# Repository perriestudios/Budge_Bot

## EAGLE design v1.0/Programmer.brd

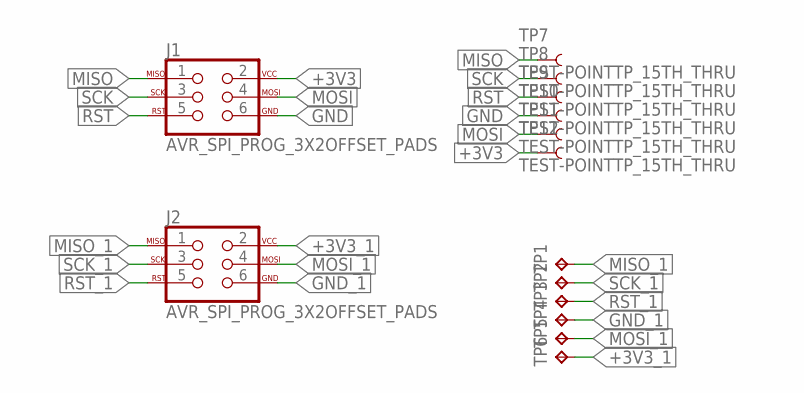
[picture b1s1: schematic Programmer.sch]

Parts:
J1, J2: AVR_SPI_PROG_3X2OFFSET_PADS; 2X3_OFFSET
TP1, TP2, TP3, TP4, TP5, TP6: TPTP12SQ; TP12SQ
TP7, TP8, TP9, TP10, TP11, TP12: TEST-POINTTP_15TH_THRU; TP_15TH

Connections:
+3V3: J1.2, TP12.P$1
+3V3_1: J2.2, TP6.TP
GND: J1.6, TP10.P$1
GND_1: J2.6, TP4.TP
MISO: J1.1, TP7.P$1
MISO_1: J2.1, TP1.TP
MOSI: J1.4, TP11.P$1
MOSI_1: J2.4, TP5.TP
RST: J1.5, TP9.P$1
RST_1: J2.5, TP3.TP
SCK: J1.3, TP8.P$1
SCK_1: J2.3, TP2.TP

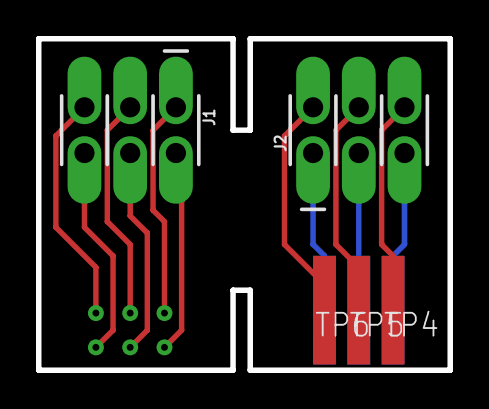
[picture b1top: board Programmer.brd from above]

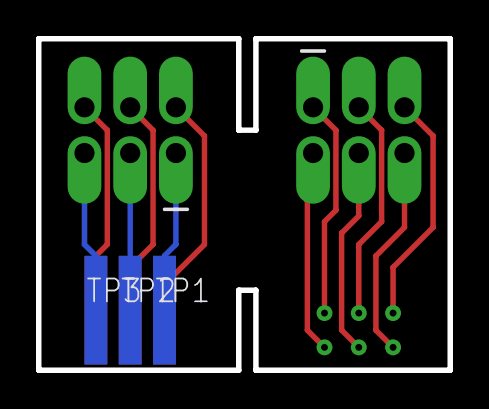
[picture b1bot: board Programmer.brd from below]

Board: 2 copper layers, 22.9 x 18.4 mm, 14 parts (3 on the bottom side), 12 nets.

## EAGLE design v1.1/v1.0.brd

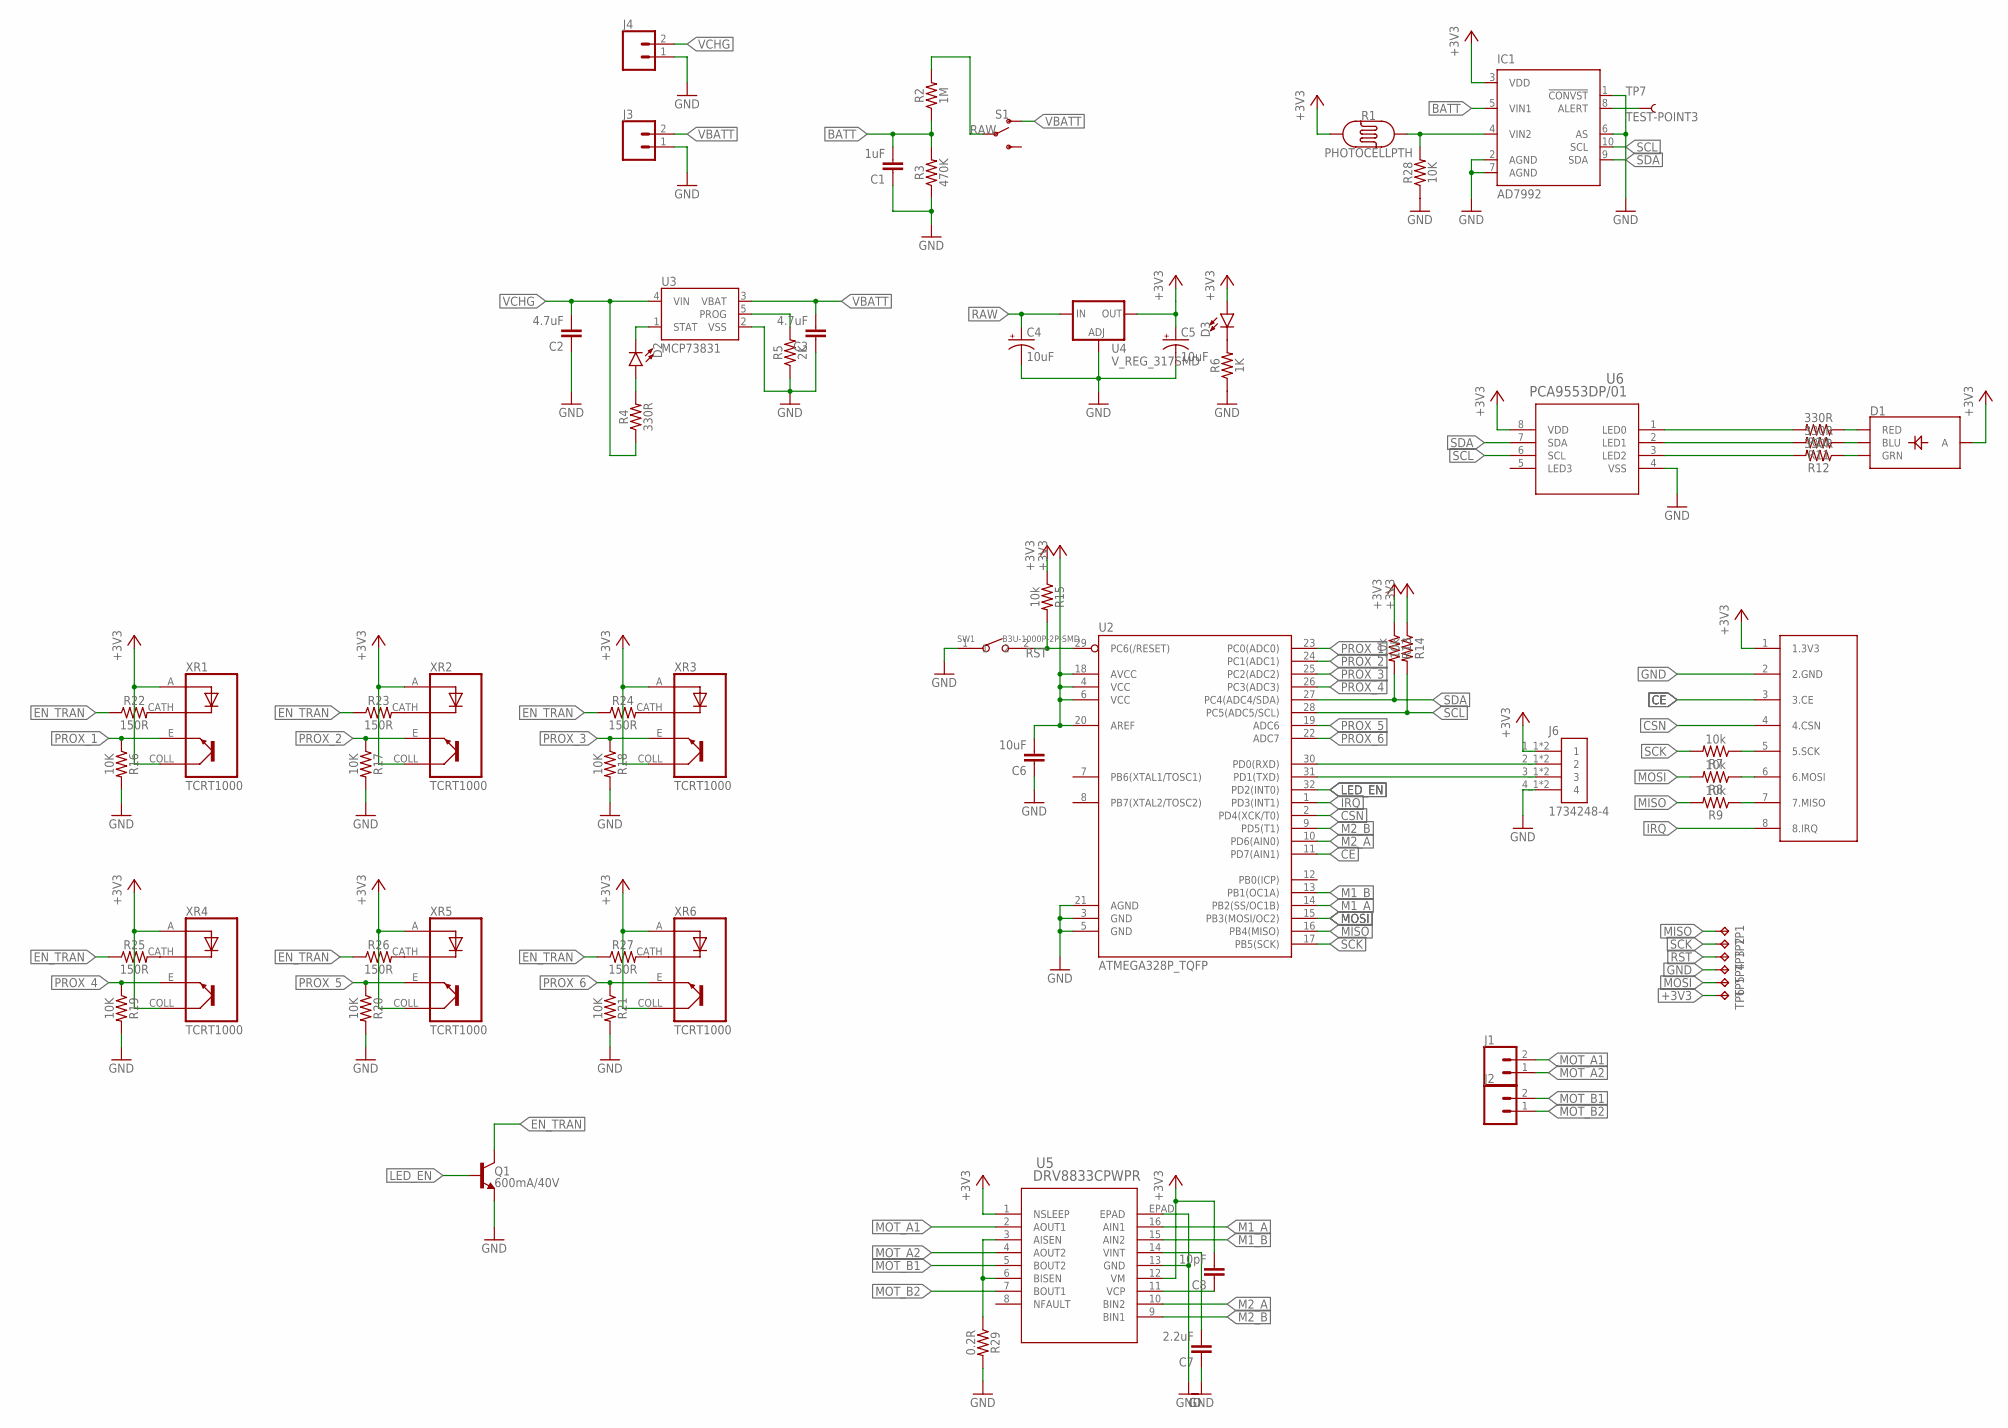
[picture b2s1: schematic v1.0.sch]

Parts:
C1: 1uF; C0603
C2, C3: 4.7uF; C0603
C4, C5: 10uF; EIA3216
C6: 10uF; C0603
C7: 2.2uF; C0603
C8: 10pF; C0603
D1: LED-RGB-CASMD; LED-TRICOLOR-SMD
D2, D3: LED0603; LED-0603
IC1: AD7992; MSOP10
J1, J2, J3, J4: CONN_02; 1X02
J6: 1734248-4; TE_1734248-4
Q1: 600mA/40V; SOT23-3
R1: PHOTOCELLPTH; PHOTOCELL
R2: 1M; 0402
R3: 470K; 0402
R4, R10, R11, R12: 330R; 0402
R5: 2K; 0402
R6: 1K; 0402
R7, R8, R9, R13, R14, R15: 10k; 0402
R16, R17, R18, R19, R20, R21, R28: 10K; 0402
R22, R23, R24, R25, R26, R27: 150R; 0402
R29: 0.2R; 0402
S1: SWITCH-SPDT-SMD-RIGHT-ANGLE; SWITCH_SPST_SMD_A
SW1: B3U-1000P-2P-SMD; SW2-2.6-3.0X2.5X1.2+0.4MM
TP1, TP2, TP3, TP4, TP5, TP6: TPB1,27; B1,27
TP7: TEST-POINT3; PAD.03X.03
U2: ATMEGA328P_TQFP; TQFP32-08
U3: MCP73831; SOT23-5
U4: V_REG_317SMD; SOT223
U5: DRV8833CPWPR; PWP16_2P31X2P46
U6: PCA9553DP/01; SOT505-1
U$1: NRF24L01+
XR1, XR2, XR3, XR4, XR5, XR6: TCRT1000; XDCR_TCRT1000

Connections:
+3V3: C5.+, C6.2, C8.2, D1.A, D3.A, IC1.3 (VDD), J6.1_1 (1), J6.1_2 (1), R1.1, R13.1, R14.1, R15.1, TP6.TP, U2.4 (VCC), U2.6 (VCC), U2.18 (AVCC), U2.20 (AREF), U4.2 (OUT), U5.1 (NSLEEP), U5.12 (VM), U6.8 (VDD), U$1.1 (1.3V3), XR1.A, XR1.COLL (CO), XR2.A, XR2.COLL (CO), XR3.A, XR3.COLL (CO), XR4.A, XR4.COLL (CO), XR5.A, XR5.COLL (CO), XR6.A, XR6.COLL (CO)
BATT: C1.2, IC1.5 (VIN1), R2.1, R3.2
CE: U2.11 (PD7(AIN1)), U$1.3 (3.CE)
CSN: U2.2 (PD4(XCK/T0)), U$1.4 (4.CSN)
EN_TRAN: Q1.3 (C), R22.1, R23.1, R24.1, R25.1, R26.1, R27.1
GND: C1.1, C2.1, C3.1, C4.-, C5.-, C6.1, C7.1, IC1.1 (!CONVST), IC1.2 (AGND), IC1.6 (AS), IC1.7 (AGND), J3.1, J4.1, J6.4_1 (4), J6.4_2 (4), Q1.2 (E), R3.1, R5.1, R6.1, R16.2, R17.2, R18.2, R19.2, R20.2, R21.2, R28.1, R29.2, SW1.1, TP4.TP, U2.3 (GND), U2.5 (GND), U2.21 (AGND), U3.2 (VSS), U4.1 (ADJ), U5.13 (GND), U5.EPAD, U6.4 (VSS), U$1.2 (2.GND)
IRQ: U2.1 (PD3(INT1)), U$1.8 (8.IRQ)
LED_EN: Q1.1 (B), U2.32 (PD2(INT0))
M1_A: U2.14 (PB2(SS/OC1B)), U5.16 (AIN1)
M1_B: U2.13 (PB1(OC1A)), U5.15 (AIN2)
M2_A: U2.10 (PD6(AIN0)), U5.10 (BIN2)
M2_B: U2.9 (PD5(T1)), U5.9 (BIN1)
MISO: R9.2, TP1.TP, U2.16 (PB4(MISO))
MOSI: R8.2, TP5.TP, U2.15 (PB3(MOSI/OC2))
MOT_A1: J1.2, U5.2 (AOUT1)
MOT_A2: J1.1, U5.4 (AOUT2)
MOT_B1: J2.2, U5.5 (BOUT2)
MOT_B2: J2.1, U5.7 (BOUT1)
unnamed: R7.1, U$1.5 (5.SCK)
unnamed: R8.1, U$1.6 (6.MOSI)
unnamed: D3.C, R6.2
unnamed: D2.C, U3.1 (STAT)
unnamed: D2.A, R4.2
unnamed: R9.1, U$1.7 (7.MISO)
unnamed: D1.R (RED), R10.1
unnamed: D1.B (BLU), R11.1
unnamed: R5.2, U3.5 (PROG)
unnamed: D1.G (GRN), R12.1
unnamed: R29.1, U5.3 (AISEN), U5.6 (BISEN)
unnamed: IC1.4 (VIN2), R1.2, R28.2
unnamed: IC1.8 (ALERT), TP7.P$1
unnamed: C7.2, U5.14 (VINT)
unnamed: C8.1, U5.11 (VCP)
unnamed: J6.3_1 (3), J6.3_2 (3), U2.31 (PD1(TXD))
unnamed: J6.2_1 (2), J6.2_2 (2), U2.30 (PD0(RXD))
unnamed: R22.2, XR1.CATH (C)
unnamed: R23.2, XR2.CATH (C)
unnamed: R24.2, XR3.CATH (C)
unnamed: R25.2, XR4.CATH (C)
unnamed: R26.2, XR5.CATH (C)
unnamed: R27.2, XR6.CATH (C)
PROX_1: R16.1, U2.23 (PC0(ADC0)), XR1.E
PROX_2: R17.1, U2.24 (PC1(ADC1)), XR2.E
PROX_3: R18.1, U2.25 (PC2(ADC2)), XR3.E
PROX_4: R19.1, U2.26 (PC3(ADC3)), XR4.E
PROX_5: R20.1, U2.19 (ADC6), XR5.E
PROX_6: R21.1, U2.22 (ADC7), XR6.E
RAW: C4.+, R2.2, S1.2, U4.3 (IN)
RGB-1: R10.2, U6.1 (LED0)
RGB-2: R11.2, U6.2 (LED1)
RGB-3: R12.2, U6.3 (LED2)
RST: R15.2, SW1.2, TP3.TP, U2.29 (PC6(/RESET))
SCK: R7.2, TP2.TP, U2.17 (PB5(SCK))
SCL: IC1.10 (SCL), R14.2, U2.28 (PC5(ADC5/SCL)), U6.6 (SCL)
SDA: IC1.9 (SDA), R13.2, U2.27 (PC4(ADC4/SDA)), U6.7 (SDA)
VBATT: C3.2, J3.2, S1.1 (O), U3.3 (VBAT)
VCHG: C2.2, J4.2, R4.1, U3.4 (VIN)

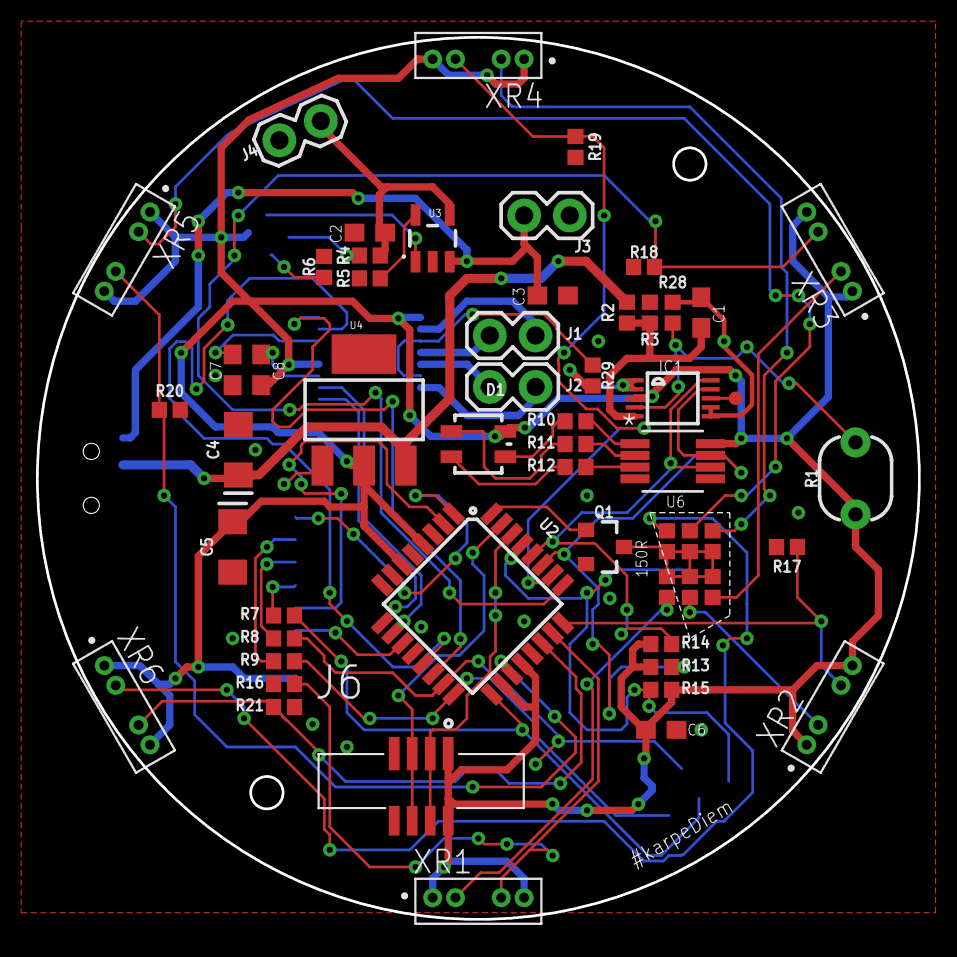
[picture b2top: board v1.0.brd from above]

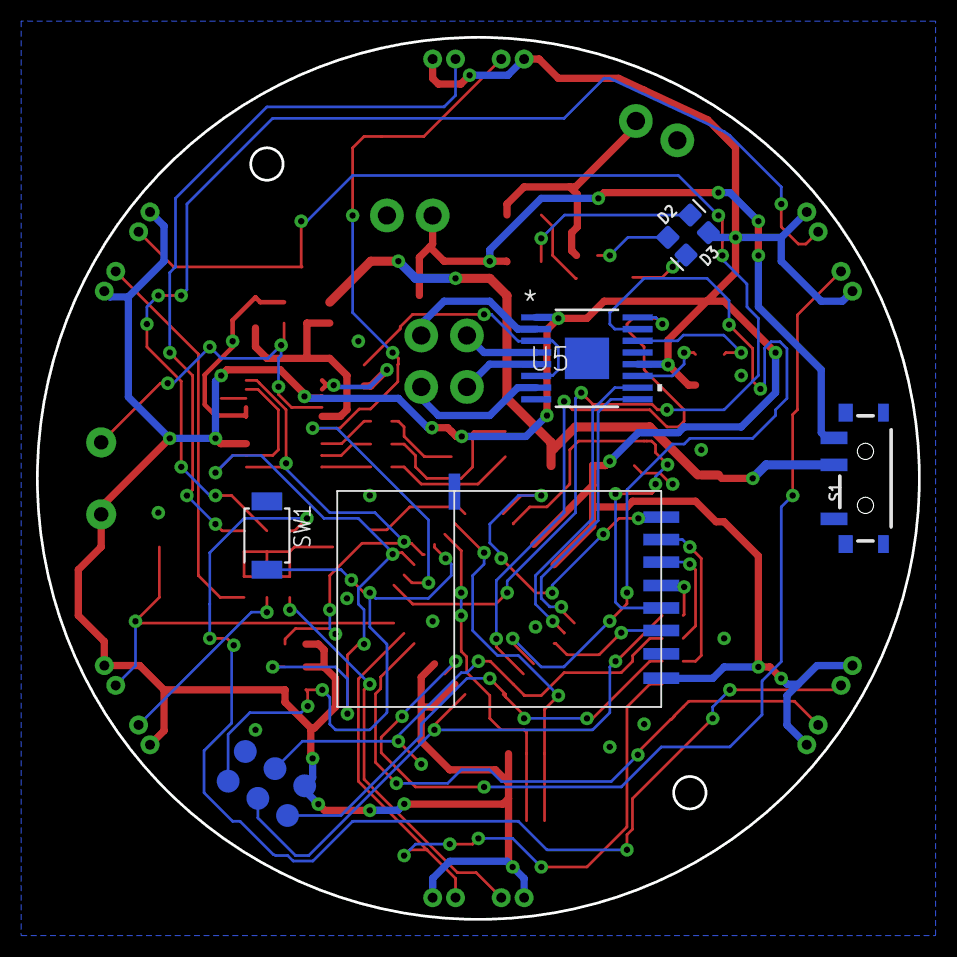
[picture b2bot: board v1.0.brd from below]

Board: 2 copper layers, 49.0 x 49.0 mm, 68 parts (12 on the bottom side), 57 nets.

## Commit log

2020-11-17 Added the files

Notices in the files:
parts and their libraries:
SparkFun-Connectors: Licensing: Creative Commons ShareAlike 4.0 International - https://creativecommons.org/licenses/by-sa/4.0
